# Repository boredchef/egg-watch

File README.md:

# egg-watch
a tamagotchi pet bird that poops and chirps

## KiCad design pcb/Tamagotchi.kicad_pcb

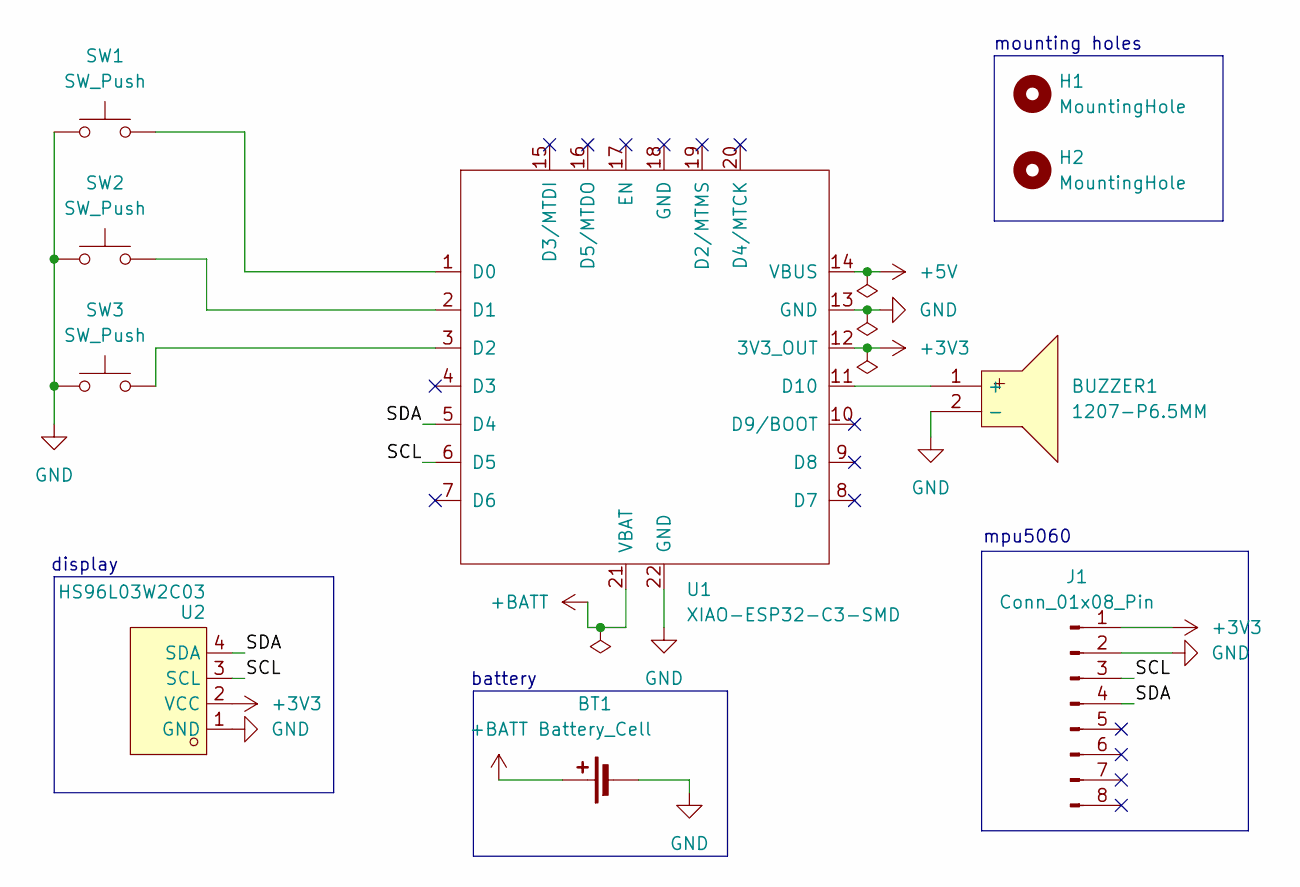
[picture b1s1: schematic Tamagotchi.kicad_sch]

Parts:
BT1: Battery_Cell; PinHeader_1x02_P2.54mm_Vertical
BUZZER1: 1207-P6.5MM; Buzzer_12x9.5RM7.6; MPN 1207-P6.5MM; LCSC Part C49246964
H1, H2: MountingHole; MountingHole_3.2mm_M3
J1: Conn_01x08_Pin; PinHeader_1x08_P2.54mm_Vertical
SW1, SW2, SW3: SW_Push; SW-TH_4P-L4.5-W4.5-P3.00-LS4.8
U1: XIAO-ESP32-C3-SMD; XIAO-ESP32-C3-DIP-SMD
U2: HS96L03W2C03; OLED-TH_L27.8-W27.2-P2.54_C9900033791; MPN HS96L03W2C03; LCSC Part C5248080

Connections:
+3V3: J1.1, U1.12 (3V3_OUT), U2.2 (VCC)
+5V: U1.14 (VBUS)
+BATT: BT1.1 (+), U1.21 (VBAT)
/SCL: J1.3, U1.6 (D5), U2.3 (SCL)
/SDA: J1.4, U1.5 (D4), U2.4 (SDA)
GND: BT1.2 (-), BUZZER1.2 (-), J1.2, SW1.1, SW2.1, SW3.1, U1.13 (GND), U1.22 (GND), U2.1 (GND)
unnamed: BUZZER1.1 (+), U1.11 (D10)
unnamed: SW1.2, U1.1 (D0)
unnamed: SW2.2, U1.2 (D1)
unnamed: SW3.2, U1.3 (D2)

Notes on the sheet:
display
mounting holes
battery
mpu5060

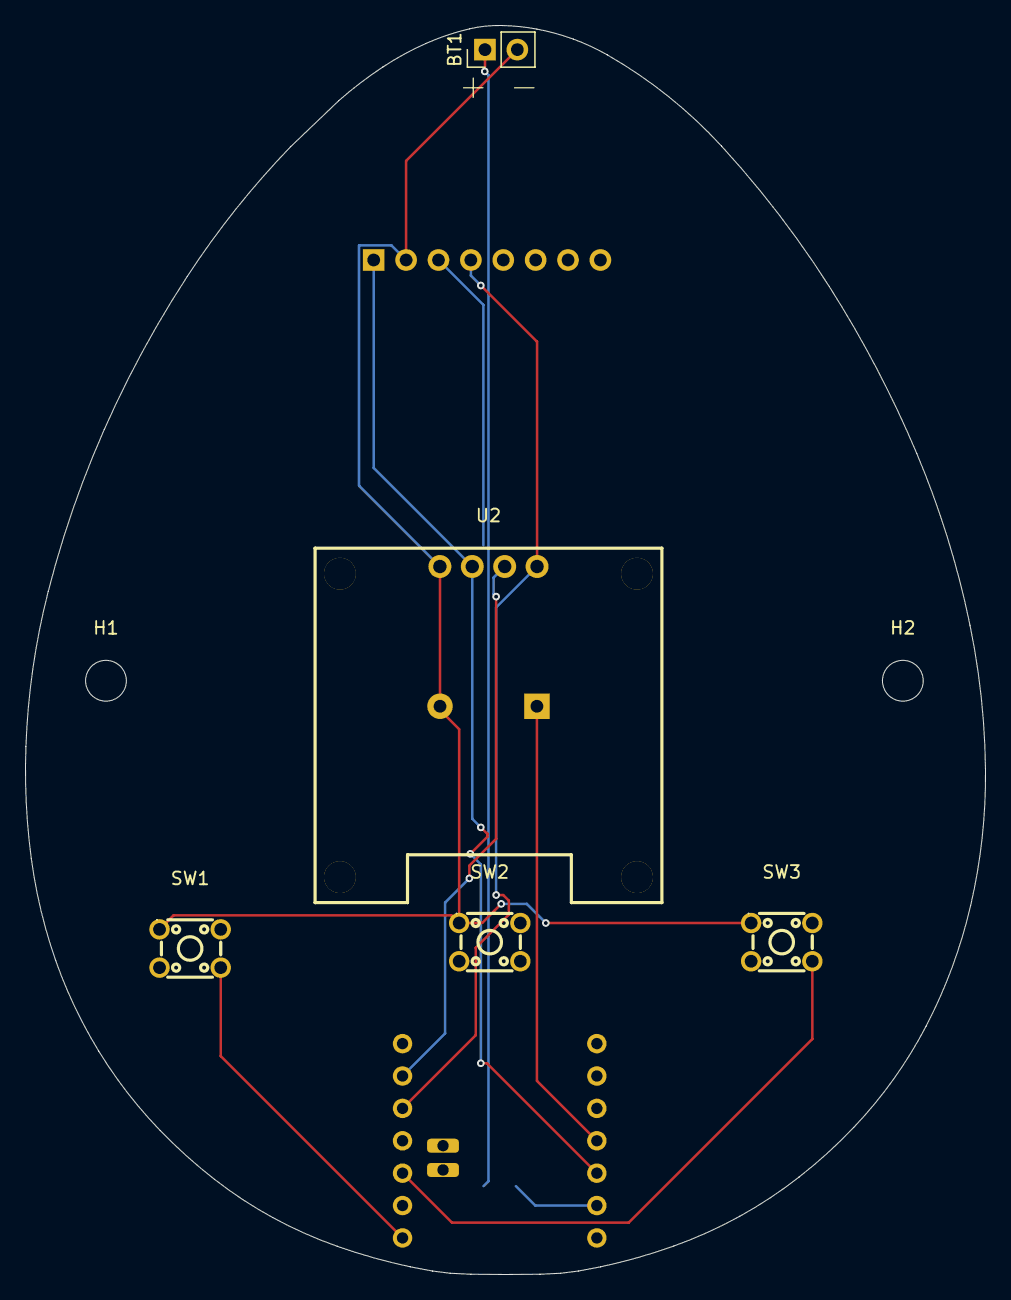
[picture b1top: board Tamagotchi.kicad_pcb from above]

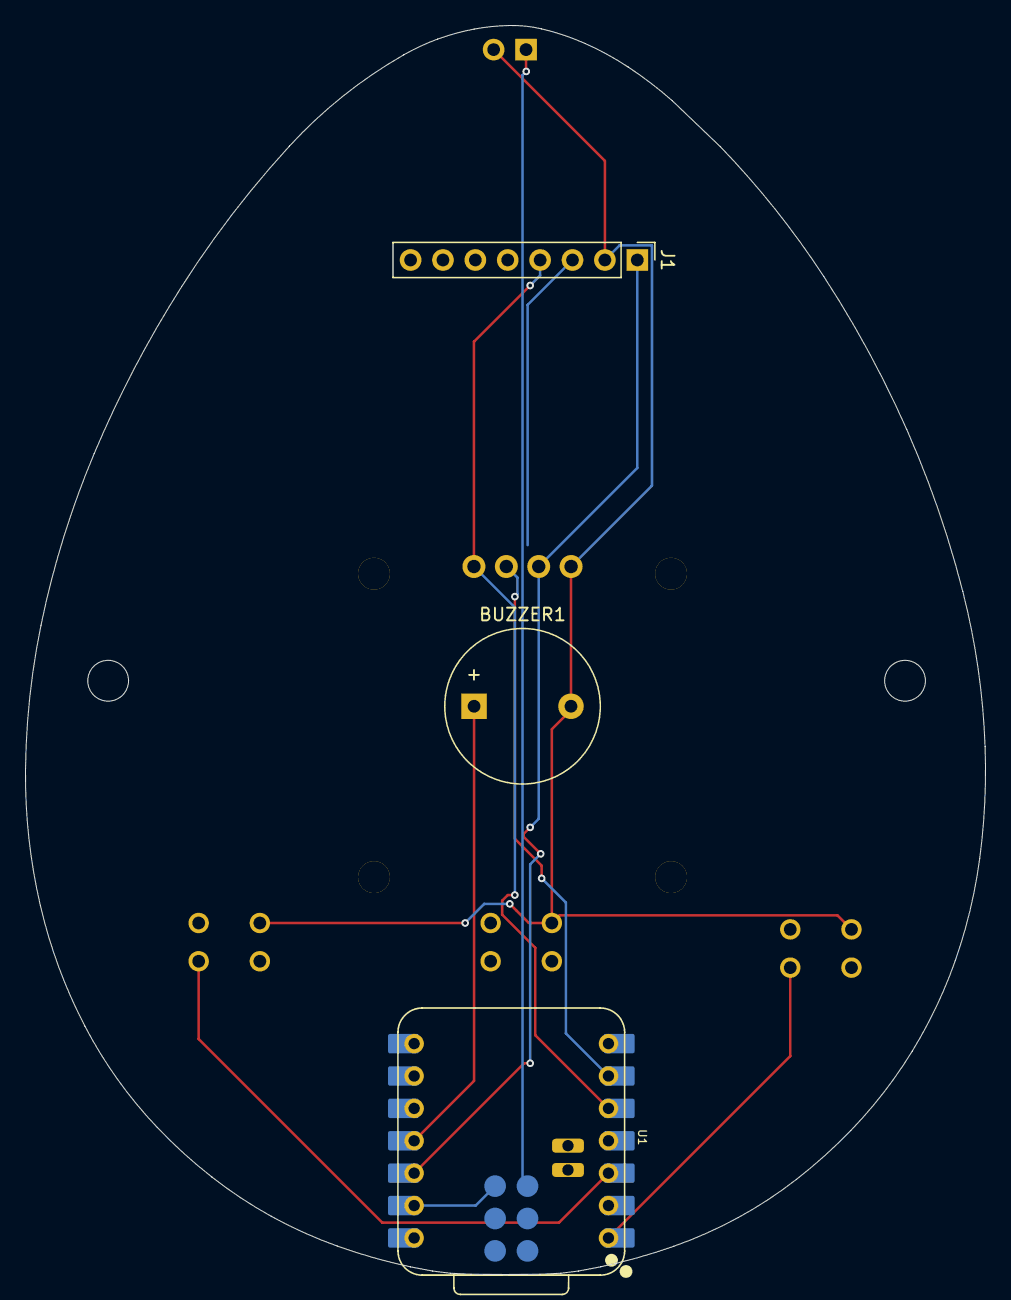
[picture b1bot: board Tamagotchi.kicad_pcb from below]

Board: 2 copper layers, 75.3 x 98.0 mm, 10 parts (3 on the bottom side), 9 nets.
